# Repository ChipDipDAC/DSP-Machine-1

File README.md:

# DSP-Machine-1
Hi-Res Streamer - Power Amplifier for Raspberry Pi<br>
<a class="link" href="https://www.chipdip.ru/catalog-show/for-you-projects?p.0=ChipDipDac"><strong>DSP Machine 1</strong></a> - cтример, цифроаналоговый преобразователь ЦАП, аудиопроцессор, усилитель для микрокомпьютеров Raspberry Pi.<br />
Для построения стримера-усилителя вы можете использовать любой микрокомпьютер Raspberry Pi 2 или 3. Микрокомпьютер устанавливается на 40-пиновый разъем аудио карты. В качестве ПО используйте любой плеер или ОС образ, которых записан на микроSD карточку для Raspberry Pi. Операционные системы автоматически определяют аудиокарту ChipDip DAC и настраивают вывод звука именно на неё. В некоторых плеерах может понадобится выбрать в качестве устройства вывода звука - ChipDip DAC.<br />
<br />
- Plug and Play не требует пайки<br />
- Совместим с Raspberry Pi<br />
- Официальная поддержка RaspberryPi OS / Volumio3 / rAudio1 / Album Player / OpenELEC / Manjaro OS / MoOde и другими<br />
- DSP ADAU1701, чип усилителя TPA3255 для наилучшего качества звука.<br />
- Мощность 2х60 Вт<br />
- Разъемы аудиовыхода: две пары винтовых клемм (левый и правый)<br />
- Встроенная EEPROM для автоматической настройки ОС (с защитой от записи).<br />
- Автоматическое переключение частот в соответствии с входными сигналами I2S.<br />
- Диапазон частот дискретизации и разрядности от 44,1кГц/16 бит до 192кГц/32 бит<br />
- Совместим с ПО SigmaStudio и ChipStudio для перестройки аудиопроцессора<br />
<br />
Задать вопросы можно на форуме в разделе <a class="link" href="https://forum.chipdip.ru/index.php#chipdip-dac.39">ChipDip DAC</a>
<p></p>

<p></p>

<h2>Что под крышкой *</h2>

<p></p>

<p></p>
* Микрокомпьютер Raspberry Pi в комплект не входит.

<h2>Сравнительная таблица</h2>

<table class="user_t">
	<tbody>
		<tr>
			<td class="tcenter">&nbsp;</td>
			<td class="tcenter">DSP Machine 1</td>
			<td class="tcenter">DSP Machine 2</td>
			<td class="tcenter">DSP Machine 3</td>
		</tr>
		<tr>
			<td class="tcenter">Темброблок</td>
			<td class="tcenter">+</td>
			<td class="tcenter">+</td>
			<td class="tcenter">+</td>
		</tr>
		<tr>
			<td class="tcenter">SuperBass</td>
			<td class="tcenter">+</td>
			<td class="tcenter">+</td>
			<td class="tcenter">+</td>
		</tr>
		<tr>
			<td class="tcenter">Mute</td>
			<td class="tcenter">+</td>
			<td class="tcenter">+</td>
			<td class="tcenter">+</td>
		</tr>
		<tr>
			<td class="tcenter">Блок питания</td>
			<td class="tcenter">+</td>
			<td class="tcenter">+</td>
			<td class="tcenter">+</td>
		</tr>
		<tr>
			<td class="tcenter">Корректное выключение</td>
			<td class="tcenter">+</td>
			<td class="tcenter">+</td>
			<td class="tcenter">+</td>
		</tr>
		<tr>
			<td class="tcenter">Линейный выход</td>
			<td class="tcenter">-</td>
			<td class="tcenter">+</td>
			<td class="tcenter">+</td>
		</tr>
		<tr>
			<td class="tcenter">Усилитель мощности</td>
			<td class="tcenter">+</td>
			<td class="tcenter">-</td>
			<td class="tcenter">-</td>
		</tr>
		<tr>
			<td class="tcenter">Выход SPDIF</td>
			<td class="tcenter">-</td>
			<td class="tcenter">-</td>
			<td class="tcenter">+</td>
		</tr>
		<tr>
			<td class="tcenter">Выход Toslink</td>
			<td class="tcenter">-</td>
			<td class="tcenter">-</td>
			<td class="tcenter">+</td>
		</tr>
		<tr>
			<td class="tcenter">SigmaStudio</td>
			<td class="tcenter">+</td>
			<td class="tcenter">-</td>
			<td class="tcenter">+</td>
		</tr>
		<tr>
			<td class="tcenter">PurePathStudio</td>
			<td class="tcenter">-</td>
			<td class="tcenter">+</td>
			<td class="tcenter">-</td>
		</tr>
		<tr>
			<td class="tcenter">ChipStudio</td>
			<td class="tcenter">+</td>
			<td class="tcenter">+</td>
			<td class="tcenter">+</td>
		</tr>
	</tbody>
</table>
<br />

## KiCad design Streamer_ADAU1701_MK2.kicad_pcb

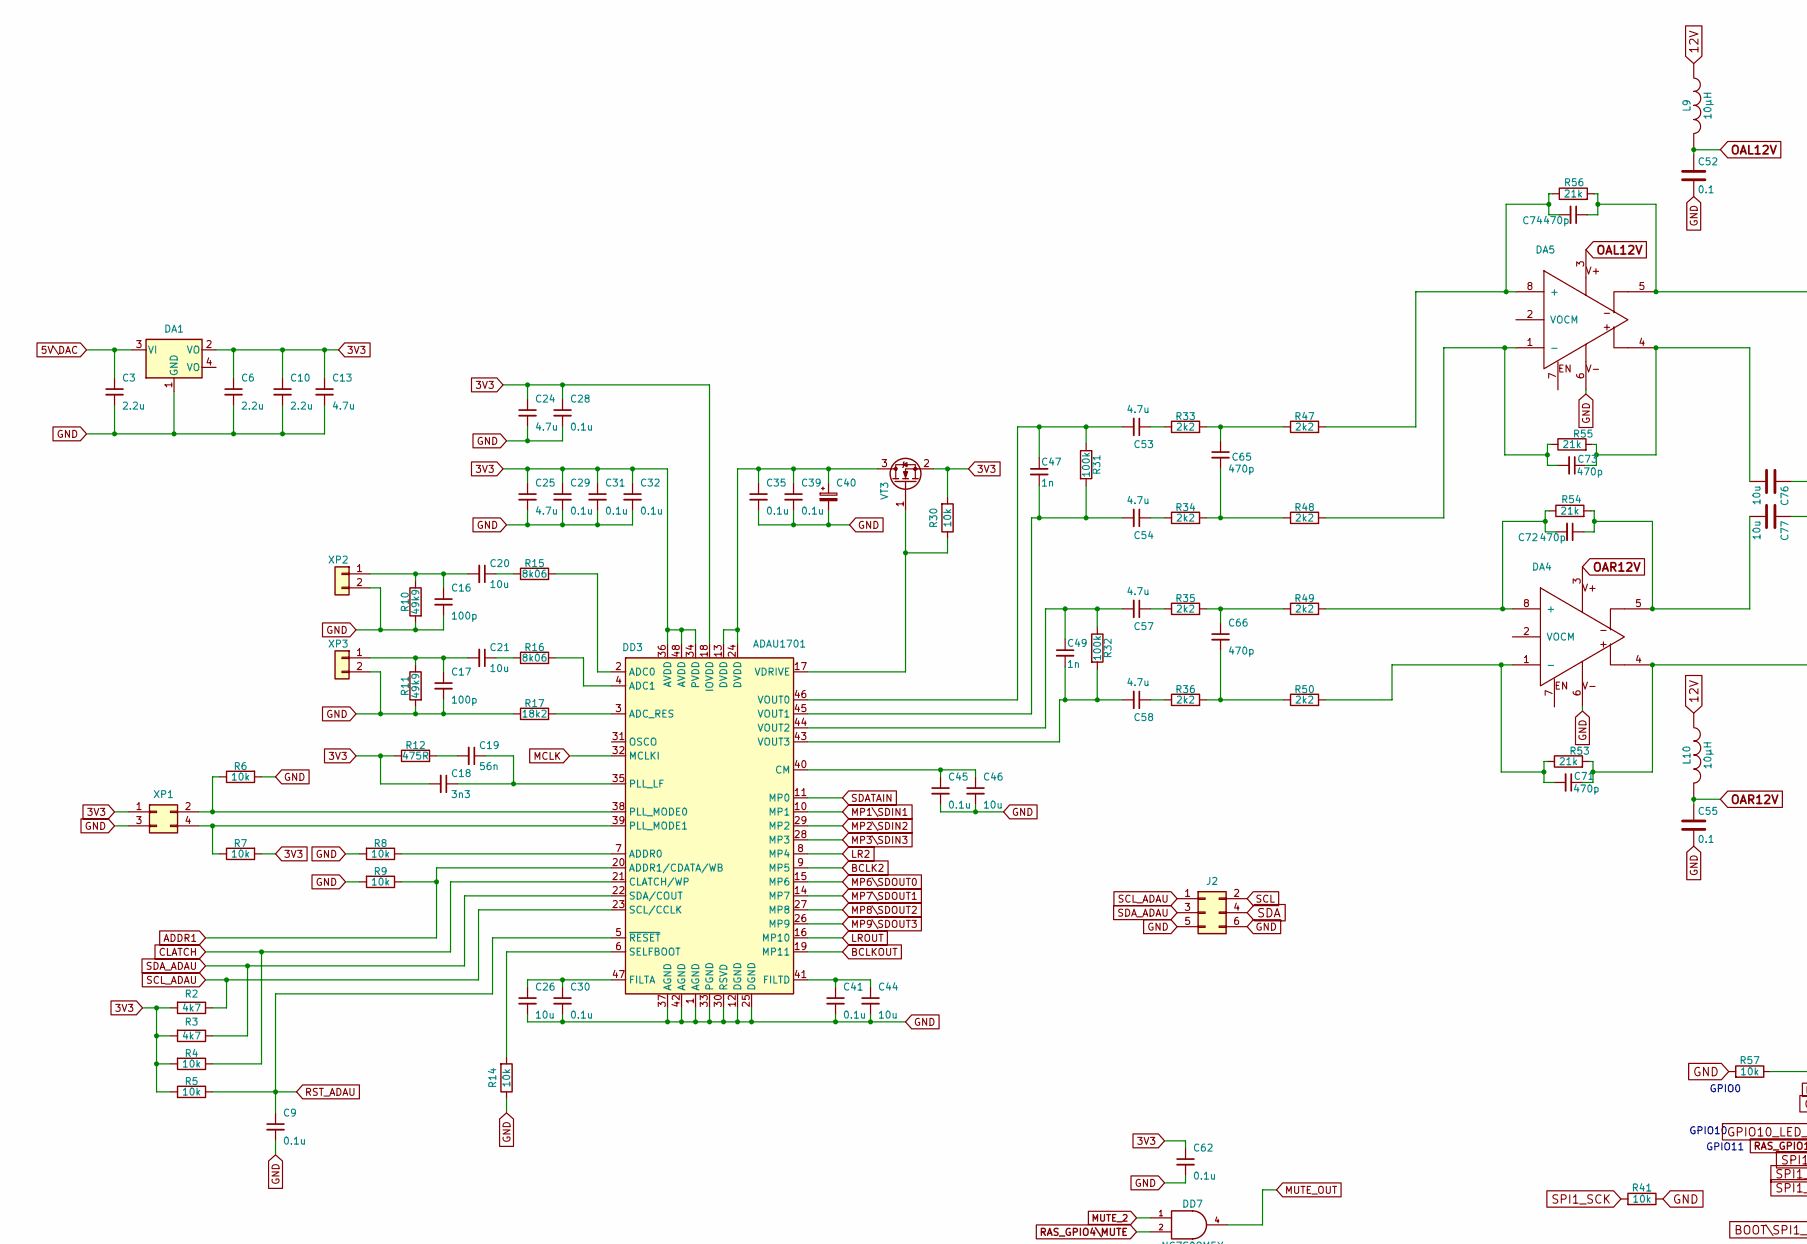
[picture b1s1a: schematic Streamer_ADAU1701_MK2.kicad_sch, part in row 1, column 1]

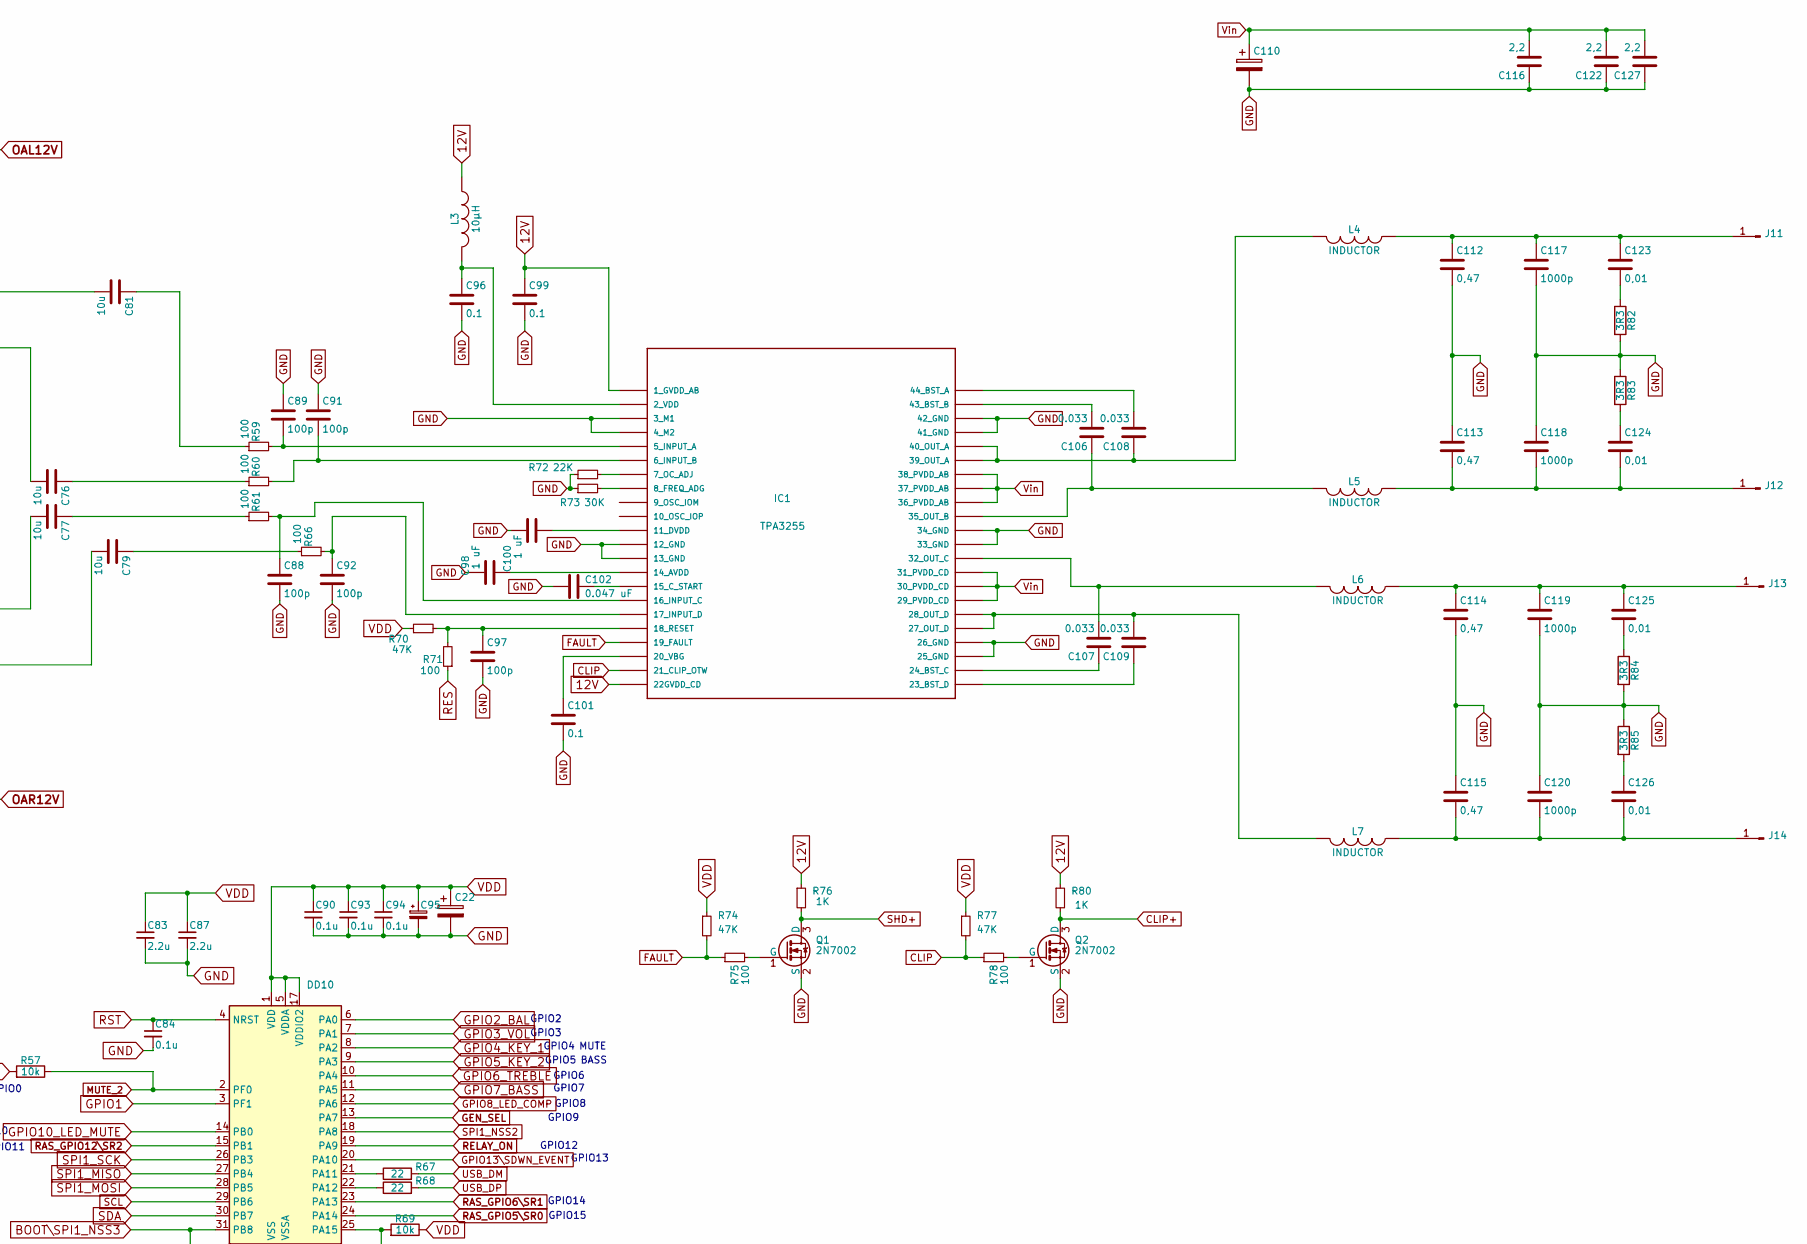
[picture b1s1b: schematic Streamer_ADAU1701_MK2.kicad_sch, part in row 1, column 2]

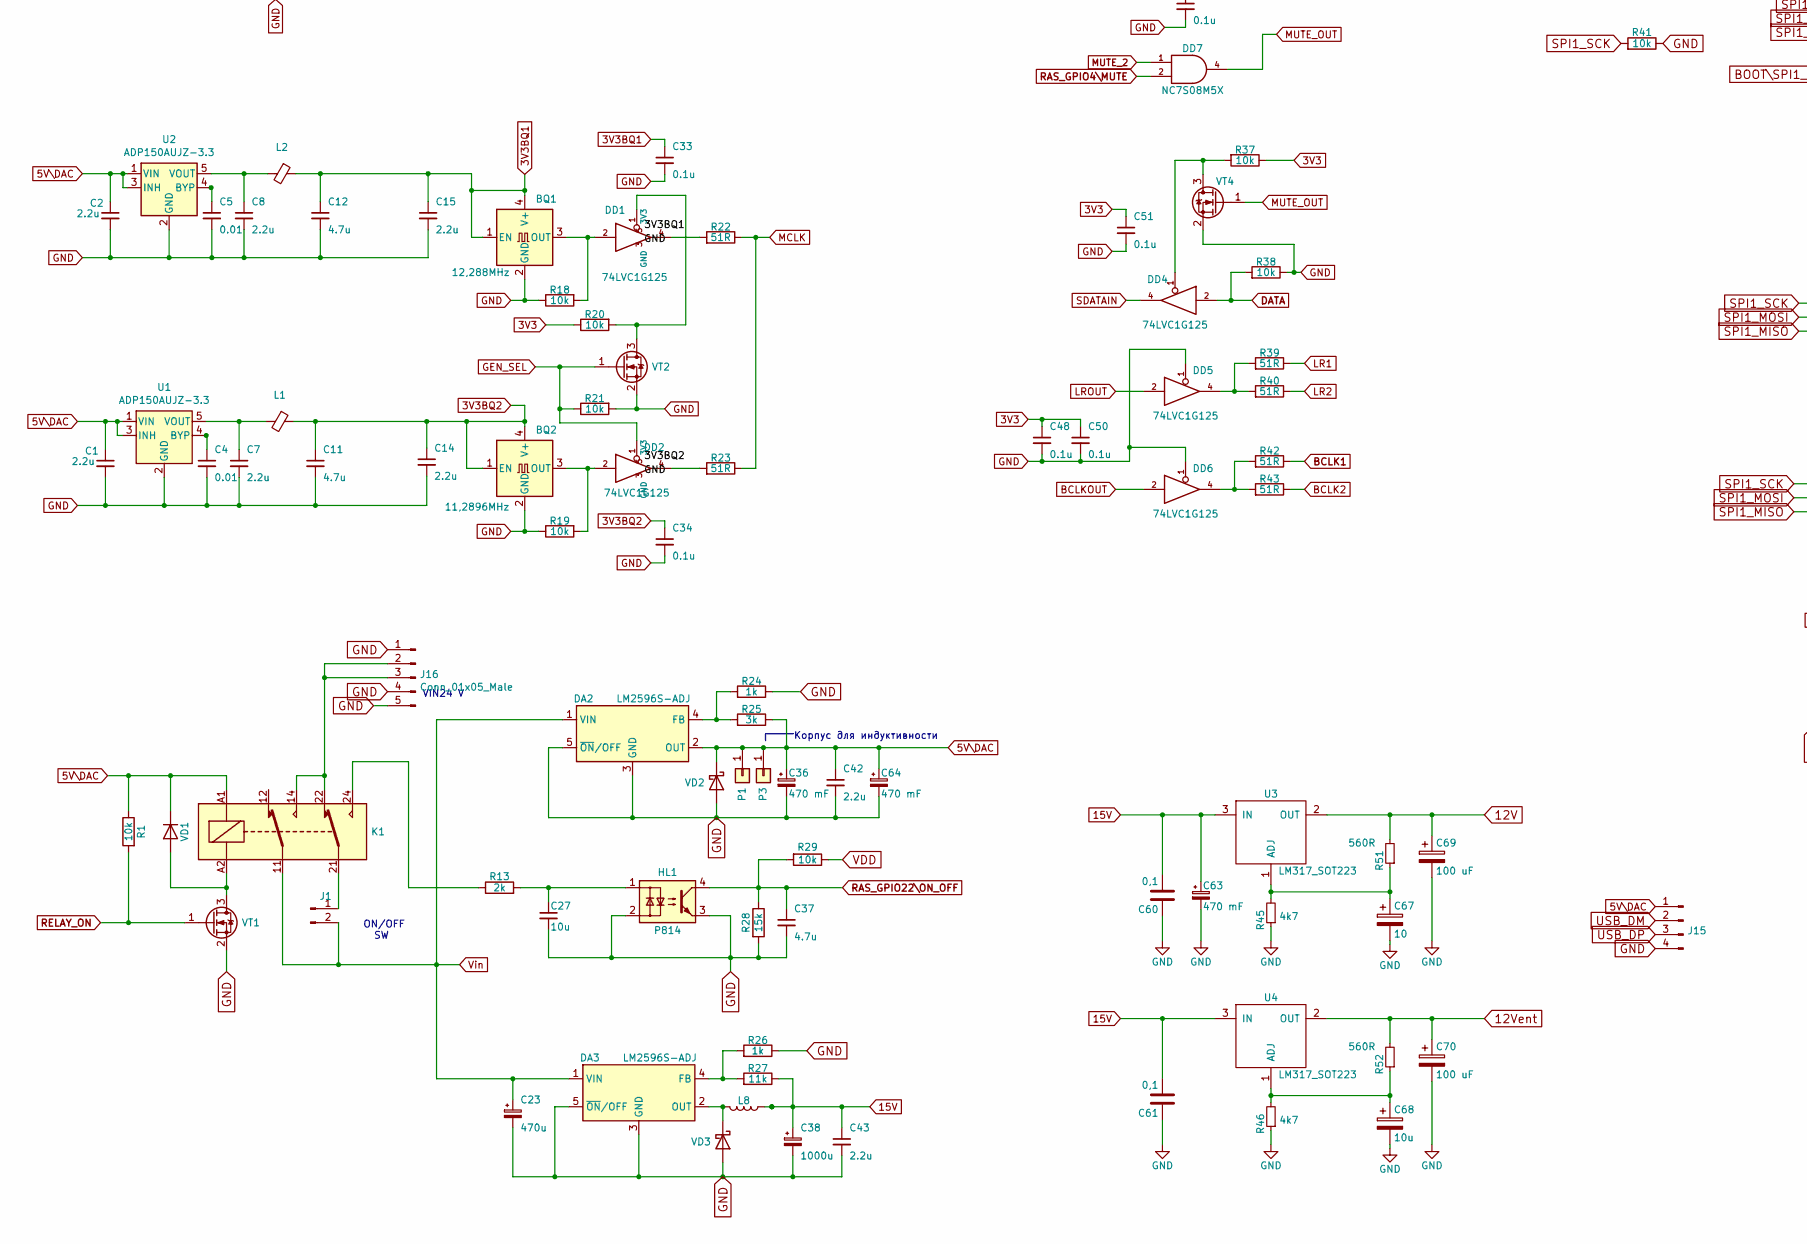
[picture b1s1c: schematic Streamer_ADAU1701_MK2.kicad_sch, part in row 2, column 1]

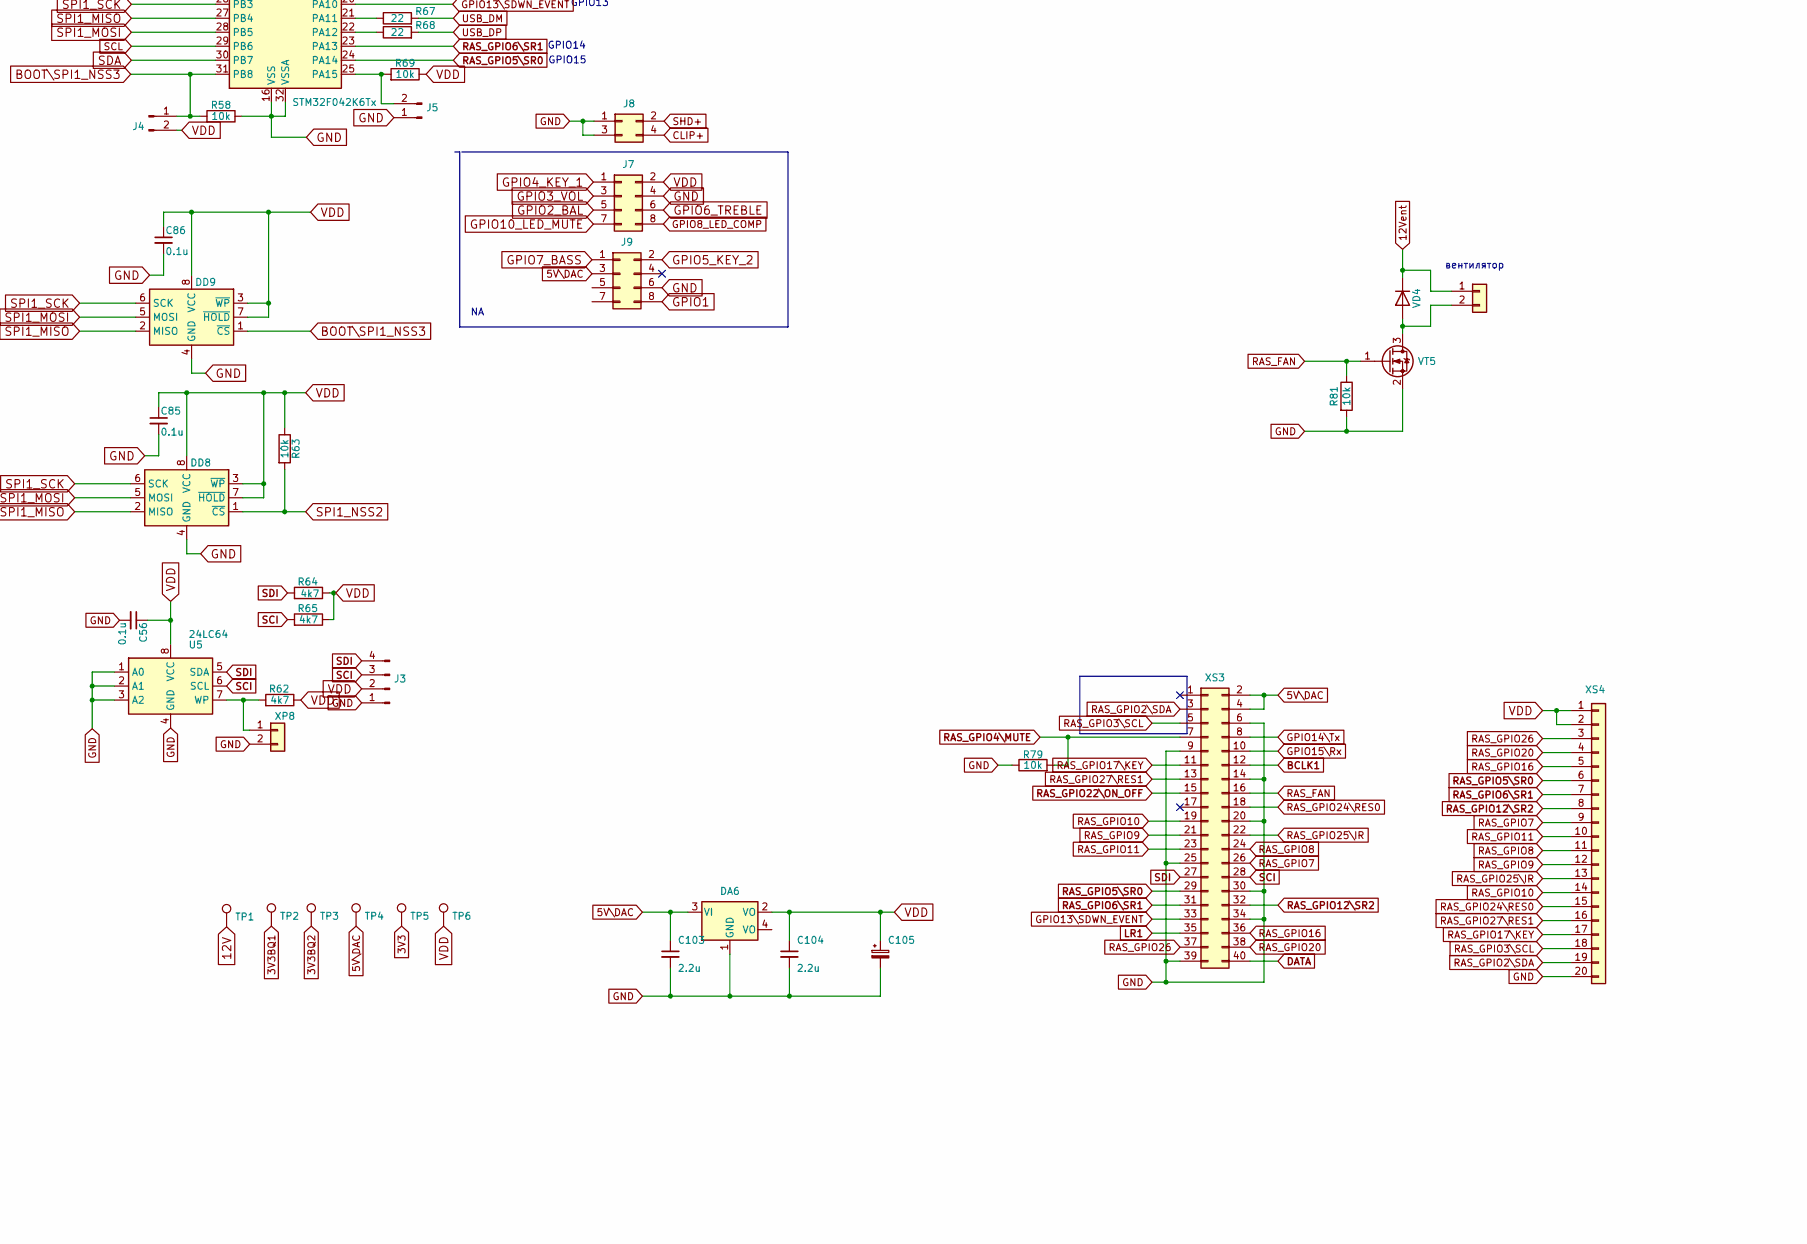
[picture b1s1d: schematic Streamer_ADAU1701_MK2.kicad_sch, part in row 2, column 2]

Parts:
BQ1: 12,288MHz; Oscillator_SMD_Fordahl_DFAS2-4Pin_7.3x5.1mm_HandSoldering
BQ2: 11,2896MHz; Oscillator_SMD_Fordahl_DFAS2-4Pin_7.3x5.1mm_HandSoldering
C1, C2, C3, C6, C7, C8, C10, C14, C15, C42, C43, C83, C87, C103, C104: 2.2u; C_0603_1608Metric_Pad1.05x0.95mm_HandSolder
C4, C5: 0.01; C_0603_1608Metric_Pad1.05x0.95mm_HandSolder
C9, C29, C30, C31, C32, C33, C34, C35, C39, C41, C45, C48, C50, C51, C56, C62, C84, C85, C86, C90, C93, C94: 0.1u; C_0603_1608Metric_Pad1.05x0.95mm_HandSolder
C11, C12, C13, C24, C25, C37: 4.7u; CP_EIA-3216-18_Kemet-A_Pad1.58x1.35mm_HandSolder
C16, C17, C88, C89, C91, C92, C97: 100p; C_0603_1608Metric_Pad1.05x0.95mm_HandSolder
C18: 3n3; C_0603_1608Metric_Pad1.05x0.95mm_HandSolder
C19: 56n; C_0603_1608Metric_Pad1.05x0.95mm_HandSolder
C20, C21, C26, C27, C44, C46: 10u; C_0603_1608Metric_Pad1.05x0.95mm_HandSolder
C22, C40, C95, C105, C110: (no value)
C23: 470u; CP_Radial_D10.0mm_P5.00mm
C28: 0.1u; C_0805_2012Metric
C36, C63, C64: 470 mF; CP_Radial_D10.0mm_P5.00mm
C38: 1000u; CP_Radial_D10.0mm_P5.00mm
C47, C49: 1n; C_Disc_D4.7mm_W2.5mm_P5.00mm
C52, C55, C96, C99, C101: 0.1; C_0603_1608Metric_Pad1.05x0.95mm_HandSolder
C53, C54, C57, C58: 4.7u; CP_Radial_D5.0mm_P2.50mm
C60, C61: 0,1; C_0603_1608Metric_Pad1.05x0.95mm_HandSolder
C65, C66: 470p; C_Disc_D4.7mm_W2.5mm_P5.00mm
C67: 10; C_Radial_D5.0mm_H11.0mm_P2.00mm
C68, C76, C77, C79, C81: 10u; C_Radial_D5.0mm_H11.0mm_P2.00mm
C69: 100 uF; CP_Radial_D10.0mm_P5.00mm
C70: 100 uF; CP_Radial_D6.3mm_P2.50mm
C71, C72, C73, C74: 470p; C_0603_1608Metric_Pad1.05x0.95mm_HandSolder
C98, C100: 1 uF; C_0603_1608Metric_Pad1.05x0.95mm_HandSolder
C102: 0.047 uF; C_0603_1608Metric_Pad1.05x0.95mm_HandSolder
C106, C107, C108, C109: 0.033; C_0603_1608Metric_Pad1.05x0.95mm_HandSolder
C112, C113, C114, C115: 0,47; C_Rect_L7.2mm_W3.5mm_P5.00mm_FKS2_FKP2_MKS2_MKP2
C116, C122, C127: 2,2; C_1210_3225Metric_Pad1.42x2.65mm_HandSolder
C117, C118, C119, C120: 1000p; C_1206_3216Metric_Pad1.42x1.75mm_HandSolder
C123, C124, C125, C126: 0,01; C_0805_2012Metric_Pad1.15x1.40mm_HandSolder
DA1, DA6: LM1117-3.3; SOT-223
DA2, DA3: LM2596S-ADJ; TO-263-5_TabPin3
DA4, DA5: OPA1632-NewComponents_KiCad; MSOP-8-1EP_3x3mm_P0.65mm_EP1.95x2.15mm_ThermalVias
DD1, DD2, DD4, DD5, DD6: 74LVC1G125; SOT-23-5
DD3: ADAU1701; LQFP-48_7x7mm_P0.5mm
DD7: NC7S08M5X; SOT-23-5
DD8, DD9: 25LCxxx; SOIC-8_5.23x5.23mm_P1.27mm
DD10: STM32F042K6Tx; LQFP-32_7x7mm_P0.8mm
HL1: P814; DIP-4_W7.62mm
IC1: TPA3255; TSSOP-44_TPA255
J1, J4, J5: Conn_01x02_Male; PinHeader_1x02_P2.54mm_Vertical
J2: Conn_02x03_Odd_Even; PinHeader_2x03_P2.54mm_Vertical
J3, J15: Conn_01x04_Male; PinHeader_1x04_P2.54mm_Vertical
J7, J9: Conn_02x04_Odd_Even; PinHeader_2x04_P2.54mm_Vertical
J8: Conn_02x02_Odd_Even; PinHeader_2x02_P2.54mm_Vertical
J11, J12, J13, J14: Conn_01x01_Male; MountingHole_2.2mm_M2
J16: Conn_01x05_Male; BarrelJack_PD-40
K1: RTE2xxxx; Relay_DPDT_Schrack-RT2-FormC_RM5mm
L1, L2: (no value)
L3, L9, L10: 10μH; L_0603_1608Metric_Pad1.05x0.95mm_HandSolder
L4, L5, L6, L7: INDUCTOR; L_Toroid_Vertical_L21.6mm_W11.4mm_P7.62mm_Pulse_KM-3
L8: MMZ2012S601AT000; L_Radial_D7.8mm_P5.00mm_Fastron_07HCP
P1, P3: Conn_01x01; TestPoint_Keystone_5005-5009_Compact
Q1, Q2: 2N7002; TSOT-23
R1, R4, R5, R6, R7, R8, R9, R14, R18, R19, R20, R21, R29, R30, R37, R38, R57, R58, R63, R69, R79, R81: 10k; R_0603_1608Metric_Pad1.05x0.95mm_HandSolder
R2, R3, R45, R46, R62, R64, R65: 4k7; R_0603_1608Metric_Pad1.05x0.95mm_HandSolder
R10, R11: 49k9; R_0603_1608Metric_Pad1.05x0.95mm_HandSolder
R12: 475R; R_0603_1608Metric_Pad1.05x0.95mm_HandSolder
R13: 2k; R_0603_1608Metric_Pad1.05x0.95mm_HandSolder
R15, R16: 8k06; R_0603_1608Metric_Pad1.05x0.95mm_HandSolder
R17: 18k2; R_0603_1608Metric_Pad1.05x0.95mm_HandSolder
R22, R23, R39, R40, R42, R43: 51R; R_0603_1608Metric_Pad1.05x0.95mm_HandSolder
R24, R26: 1k; R_0603_1608Metric_Pad1.05x0.95mm_HandSolder
R25: 3k; R_0603_1608Metric_Pad1.05x0.95mm_HandSolder
R27: 11k; R_0603_1608Metric_Pad1.05x0.95mm_HandSolder
R28: 15k; R_0603_1608Metric_Pad1.05x0.95mm_HandSolder
R31, R32: 100k; R_0603_1608Metric_Pad1.05x0.95mm_HandSolder
R33, R34, R35, R36, R47, R48, R49, R50: 2k2; R_0603_1608Metric_Pad1.05x0.95mm_HandSolder
R41: 10k; R_0603_1608Metric_Pad0.98x0.95mm_HandSolder
R51, R52: 560R; R_0603_1608Metric_Pad1.05x0.95mm_HandSolder
R53, R54, R55, R56: 21k; R_Axial_DIN0204_L3.6mm_D1.6mm_P5.08mm_Horizontal
R59, R60, R61, R66, R71, R75, R78: 100; R_0603_1608Metric_Pad1.05x0.95mm_HandSolder
R67, R68: 22; R_0603_1608Metric_Pad1.05x0.95mm_HandSolder
R70, R74, R77: 47K; R_0603_1608Metric_Pad1.05x0.95mm_HandSolder
R72: 22K; R_0603_1608Metric_Pad1.05x0.95mm_HandSolder
R73: 30K; R_0603_1608Metric_Pad1.05x0.95mm_HandSolder
R76, R80: 1K; R_0603_1608Metric_Pad1.05x0.95mm_HandSolder
R82, R83, R84, R85: 3R3; R_0805_2012Metric_Pad1.15x1.40mm_HandSolder
TP1, TP2, TP3, TP4, TP5, TP6: TestPoint; TestPoint_Pad_D1.5mm
U1, U2: ADP150AUJZ-3.3; SOT-23-5
U3, U4: LM317_SOT223; SOT-223
U5: 24LC64; SOIC-8_3.9x4.9mm_P1.27mm
VD1, VD4: D; D_SOD-123
VD2, VD3: D_Schottky; D_SMC_Handsoldering
VT1, VT2, VT3, VT4, VT5: BSS138; SOT-23
XP1: Conn_02x02_Odd_Even; PinHeader_2x02_P2.54mm_Vertical
XP2, XP3, XP8, XP9: Conn_01x02; PinHeader_1x02_P2.54mm_Vertical
XS3: Conn_02x20_Odd_Even; PinSocket_2x20_P2.54mm_Vertical
XS4: Conn_01x20; Hirose_FH12-20S-0.5SH_1x20-1MP_P0.50mm_Horizontal

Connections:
3V3: C6.1, C10.1, C13.1, C18.2, C24.1, C25.1, C28.1, C29.1, C31.1, C32.1, C48.1, C50.1, C51.1, C62.1, DA1.2 (VO), DD3.18 (IOVDD), DD3.34 (PVDD), DD3.36 (AVDD), DD3.48 (AVDD), DD4.5 (3V3), DD5.5 (3V3), DD6.5 (3V3), DD7.5 (3V3), R2.2, R3.2, R4.2, R5.2, R7.2, R12.1, R20.1, R30.2, R37.1, TP5.1, VT3.2 (S), XP1.1
3V3BQ1: BQ1.1 (EN), BQ1.4 (V+), C12.1, C15.1, C33.1, DD1.5 (3V3), L2.1, TP2.1
3V3BQ2: BQ2.1 (EN), BQ2.4 (V+), C11.1, C14.1, C34.1, DD2.5 (3V3), L1.1, TP3.1
5V\DAC: C1.1, C2.1, C3.1, C36.1, C42.1, C64.1, C103.1, DA1.3 (VI), DA2.2 (OUT), DA6.3 (VI), J9.3, J15.1, K1.A1, P1.1, P3.1, R1.1, R25.1, TP4.1, U1.1 (VIN), U1.3 (INH), U2.1 (VIN), U2.3 (INH), VD1.1 (K), VD2.1 (K), XS3.2, XS3.4
12V: C69.1, C99.1, IC1.1 (1_GVDD_AB), IC1.22 (22GVDD_CD), L3.1, L9.1, L10.1, R51.2, R76.1, R80.1, TP1.1, U3.2 (OUT)
12Vent: C70.1, R52.2, U4.2 (OUT), VD4.1 (K), XP9.1
15V: C38.1, C43.1, C60.2, C61.2, C63.1, L8.1, R27.1, U3.3 (IN), U4.3 (IN); also elsewhere on the board
ADDR1: DD3.20 (ADDR1/CDATA/WB), R9.1
BCLK1: R42.1, XS3.12
BCLK2: DD3.9 (MP5), R43.1
BCLKOUT: DD3.19 (MP11), DD6.2
BOOT\SPI1_NSS3: DD9.1 (~CS), DD10.31 (PB8), J4.1, R58.2
CLATCH: DD3.21 (CLATCH/WP), R4.1
CLIP: IC1.21 (21_CLIP_OTW), R77.2, R78.1
CLIP+: J8.4, Q2.3 (D), R80.2
DATA: DD4.2, R38.2, XS3.40
FAULT: IC1.19 (19_FAULT), R74.2, R75.1
GEN_SEL: DD2.1, DD10.13 (PA7), R21.1, VT2.1 (G)
GND: BQ1.2 (GND), BQ2.2 (GND), C1.2, C2.2, C3.2, C4.2, C5.2, C6.2, C7.2, C8.2, C9.2, C10.2, C11.2, C12.2, C13.2, C14.2, C15.2, C16.2, C17.2, C22.2, C23.2, C24.2, C25.2, C26.2, C27.2, C28.2, C29.2, C30.2, C31.2, C32.2, C33.2, C34.2, C35.2, C36.2, C37.2, C38.2, C39.2, C40.2, C41.2, C42.2, C43.2, C44.2, C45.2, C46.2, C48.2, C50.2, C51.2, C52.2, C55.2, C56.2, C60.1, C61.1, C62.2, C63.2, C64.2, C67.2, C68.2, C69.2, C70.2, C83.2, C84.2, C85.2, C86.2, C87.2, C88.2, C89.1, C90.2, C91.1, C92.2, C93.2, C94.2, C95.2, C96.2, C97.2, C98.2, C99.2, C100.2, C101.2, C102.2, C103.2, C104.2, C105.2, C110.2, C112.2, C113.1, C114.2, C115.1, C116.1, C117.2, C118.1, C119.2, C120.1, C122.1, C127.1, DA1.1 (GND), DA2.3 (GND), DA2.5 (~ON/OFF), DA3.3 (GND), DA3.5 (~ON/OFF), DA4.6, DA5.6, DA6.1 (GND), DD1.3 (GND), DD2.3 (GND), DD3.1 (AGND), DD3.12 (DGND), DD3.25 (DGND), DD3.30 (RSVD), DD3.33 (PGND), DD3.37 (AGND), DD3.42 (AGND), DD4.3 (GND), DD5.1, DD5.3 (GND), DD6.1, DD6.3 (GND), DD7.3 (GND), DD8.4 (GND), DD9.4 (GND), DD10.16 (VSS), DD10.32 (VSSA), HL1.2, HL1.3, IC1.3 (3_M1), IC1.4 (4_M2), IC1.12 (12_GND), IC1.13 (13_GND), IC1.25 (25_GND), IC1.26 (26_GND), IC1.33 (33_GND), IC1.34 (34_GND), IC1.41 (41_GND), IC1.42 (42_GND), J2.5, J2.6, J3.1, J5.1, J7.4, J8.1, J8.3, J9.6, J15.4, J16.1, J16.4, J16.5, Q1.2 (S), Q2.2 (S), R6.2, R8.2, R9.2, R10.2, R11.2, R14.1, R17.1, R18.1, R19.1, R21.2, R24.1, R26.1, R28.2, R38.1, R41.1, R45.1, R46.1, R57.2, R58.1, R72.1, R73.1, R79.1, R81.2, R82.2, R83.1, R84.2, R85.1, U1.2 (GND), U2.2 (GND), U5.1 (A0), U5.2 (A1), U5.3 (A2), U5.4 (GND), VD2.2 (A), VD3.2 (A), VT1.2 (S), VT2.2 (S), VT4.2 (S), VT5.2 (S), XP1.3, XP2.2, XP3.2, XP8.2, XS3.6, XS3.9, XS3.14, XS3.20, XS3.25, XS3.30, XS3.34, XS3.39, XS4.20
GPIO1: DD10.3 (PF1), J9.8
GPIO2_BAL: DD10.6 (PA0), J7.5
GPIO3_VOL: DD10.7 (PA1), J7.3
GPIO4_KEY_1: DD10.8 (PA2), J7.1
GPIO5_KEY_2: DD10.9 (PA3), J9.2
GPIO6_TREBLE: DD10.10 (PA4), J7.6
GPIO7_BASS: DD10.11 (PA5), J9.1
GPIO8_LED_COMP: DD10.12 (PA6), J7.8
GPIO10_LED_MUTE: DD10.14 (PB0), J7.7
GPIO13\SDWN_EVENT: DD10.20 (PA10), XS3.33
GPIO14\Tx: XS3.8
GPIO15\Rx: XS3.10
LR1: R39.1, XS3.35
LR2: DD3.8 (MP4), R40.1
LROUT: DD3.16 (MP10), DD5.2
MCLK: DD3.32 (MCLKI), R22.1, R23.1
MP1\SDIN1: DD3.10 (MP1)
MP2\SDIN2: DD3.29 (MP2)
MP3\SDIN3: DD3.28 (MP3)
MP6\SDOUT0: DD3.15 (MP6)
MP7\SDOUT1: DD3.14 (MP7)
MP8\SDOUT2: DD3.27 (MP8)
MP9\SDOUT3: DD3.26 (MP9)
MUTE_2: DD7.1, DD10.2 (PF0), R57.1
MUTE_OUT: DD7.4, VT4.1 (G)
unnamed: BQ1.3 (OUT), DD1.2, R18.2
unnamed: BQ2.3 (OUT), DD2.2, R19.2
unnamed: C4.1, U1.4 (BYP)
unnamed: C5.1, U2.4 (BYP)
unnamed: C7.1, L1.2, U1.5 (VOUT)
unnamed: C8.1, L2.2, U2.5 (VOUT)
unnamed: C16.1, C20.2, R10.1, XP2.1
unnamed: C17.1, C21.2, R11.1, XP3.1
unnamed: C18.1, C19.1, DD3.35 (PLL_LF)
unnamed: C19.2, R12.2
unnamed: C20.1, R15.1
unnamed: C21.1, R16.1
unnamed: C26.1, C30.1, DD3.47 (FILTA)
unnamed: C27.1, HL1.1, R13.2
unnamed: C35.1, C39.1, C40.1, DD3.13 (DVDD), DD3.24 (DVDD), VT3.3 (D)
unnamed: C41.1, C44.1, DD3.41 (FILTD)
unnamed: C45.1, C46.1, DD3.40 (CM)
unnamed: C47.1, C53.2, DD3.46 (VOUT0), R31.1
unnamed: C47.2, C54.2, DD3.45 (VOUT1), R31.2
unnamed: C49.1, C57.2, DD3.44 (VOUT2), R32.1
unnamed: C49.2, C58.2, DD3.43 (VOUT3), R32.2
unnamed: C53.1, R33.1
unnamed: C54.1, R34.1
unnamed: C57.1, R35.1
unnamed: C58.1, R36.1
unnamed: C65.1, R33.2, R47.1
unnamed: C65.2, R34.2, R48.1
unnamed: C66.1, R35.2, R49.1
unnamed: C66.2, R36.2, R50.1
unnamed: C67.1, R45.2, R51.1, U3.1 (ADJ)
unnamed: C68.1, R46.2, R52.1, U4.1 (ADJ)
unnamed: C71.1, C79.2, DA4.4, R53.2
unnamed: C71.2, DA4.1 (-), R50.2, R53.1
unnamed: C72.1, C77.2, DA4.5, R54.2
unnamed: C72.2, DA4.8 (+), R49.2, R54.1
unnamed: C73.1, C76.2, DA5.4, R55.2
unnamed: C73.2, DA5.1 (-), R48.2, R55.1
unnamed: C74.1, C81.2, DA5.5, R56.2
unnamed: C74.2, DA5.8 (+), R47.2, R56.1
unnamed: C76.1, R60.1
unnamed: C77.1, R61.1
unnamed: C79.1, R66.1
unnamed: C81.1, R59.1
unnamed: C88.1, IC1.16 (16_INPUT_C), R61.2
unnamed: C89.2, IC1.5 (5_INPUT_A), R59.2
unnamed: C91.2, IC1.6 (6_INPUT_B), R60.2
unnamed: C92.1, IC1.17 (17_INPUT_D), R66.2
unnamed: C96.1, IC1.2 (2_VDD), L3.2
unnamed: C97.1, IC1.18 (18_RESET), R70.2, R71.2
unnamed: C98.1, IC1.14 (14_AVDD)
unnamed: C100.1, IC1.11 (11_DVDD)
unnamed: C101.1, IC1.20 (20_VBG)
unnamed: C102.1, IC1.15 (15_C_START)
unnamed 97: C106.1, IC1.35 (35_OUT_B), L5.2; also elsewhere on the board
unnamed: C106.2, IC1.43 (43_BST_B)
unnamed: C107.1, IC1.24 (24_BST_C)
unnamed 100: C107.2, IC1.32 (32_OUT_C), L6.2; also elsewhere on the board
unnamed 101: C108.1, IC1.39 (39_OUT_A), IC1.40 (40_OUT_A), L4.2; also elsewhere on the board
unnamed: C108.2, IC1.44 (44_BST_A)
unnamed: C109.1, IC1.23 (23_BST_D)
unnamed 104: C109.2, IC1.27 (27_OUT_D), IC1.28 (28_OUT_D), L7.2; also elsewhere on the board
unnamed 105: C112.1, C117.1, C123.1, J11.1, J11.J11, L4.1; also elsewhere on the board
unnamed 106: C113.2, C118.2, C124.2, J12.1, L5.1; also elsewhere on the board
unnamed 107: C114.1, C119.1, C125.1, J13.1, L6.1; also elsewhere on the board
unnamed 108: C115.2, C120.2, C126.2, J14.1, L7.1; also elsewhere on the board
unnamed: C123.2, R82.1
unnamed: C124.1, R83.2
unnamed: C125.2, R84.1
unnamed: C126.1, R85.2
unnamed: DA2.4 (FB), R24.2, R25.2
unnamed: DA3.4 (FB), R26.2, R27.2
unnamed: DD1.1, R20.2, VT2.3 (D)
unnamed: DD1.4, R22.2
unnamed: DD2.4, R23.2
unnamed: DD3.2 (ADC0), R15.2
unnamed: DD3.3 (ADC_RES), R17.2
unnamed: DD3.4 (ADC1), R16.2
unnamed: DD3.6 (SELFBOOT), R14.2
unnamed: DD3.7 (ADDR0), R8.1
unnamed: DD3.17 (VDRIVE), R30.1, VT3.1 (G)
unnamed: DD3.38 (PLL_MODE0), R6.1, XP1.2
unnamed: DD3.39 (PLL_MODE1), R7.1, XP1.4
unnamed: DD4.1, R37.2, VT4.3 (D)
unnamed: DD5.4, R39.2, R40.2
unnamed: DD6.4, R42.2, R43.2
unnamed: DD10.21 (PA11), R67.1
unnamed: DD10.22 (PA12), R68.1
unnamed: DD10.25 (PA15), J5.2, R69.2
unnamed: IC1.7 (7_OC_ADJ), R72.2
unnamed: IC1.8 (8_FREQ_ADG), R73.2
unnamed: J1.1, K1.21
unnamed: J16.2, J16.3, K1.14, K1.22
unnamed: K1.24, R13.1
unnamed: K1.A2, VD1.2 (A), VT1.3 (D)
unnamed: Q1.1 (G), R75.2
unnamed: Q2.1 (G), R78.2
unnamed: R62.2, U5.7 (WP), XP8.1
unnamed: VD4.2 (A), VT5.3 (D), XP9.2
OAL12V: C52.1, DA5.3, L9.2
OAR12V: C55.1, DA4.3, L10.2
RAS_FAN: R81.1, VT5.1 (G), XS3.16
RAS_GPIO2\SDA: XS3.3, XS4.19
RAS_GPIO3\SCL: XS3.5, XS4.18
RAS_GPIO4\MUTE: DD7.2, R79.2, XS3.7
RAS_GPIO5\SR0: DD10.24 (PA14), XS3.29, XS4.6
RAS_GPIO6\SR1: DD10.23 (PA13), XS3.31, XS4.7
RAS_GPIO7: XS3.26, XS4.9
RAS_GPIO8: XS3.24, XS4.11
RAS_GPIO9: XS3.21, XS4.12
RAS_GPIO10: XS3.19, XS4.14
RAS_GPIO11: XS3.23, XS4.10
RAS_GPIO12\SR2: DD10.15 (PB1), XS3.32, XS4.8
RAS_GPIO16: XS3.36, XS4.5
RAS_GPIO17\KEY: XS3.11, XS4.17
RAS_GPIO20: XS3.38, XS4.4
RAS_GPIO22\ON_OFF: C37.1, HL1.4, R28.1, R29.2, XS3.15
RAS_GPIO24\RES0: XS3.18, XS4.15
RAS_GPIO25\IR: XS3.22, XS4.13
RAS_GPIO26: XS3.37, XS4.3
RAS_GPIO27\RES1: XS3.13, XS4.16
RELAY_ON: DD10.19 (PA9), R1.2, VT1.1 (G)
RES: R71.1
RST: C84.1, DD10.4 (NRST)
RST_ADAU: C9.1, DD3.5 (~RESET), R5.1
SCI: J3.3, R65.2, U5.6 (SCL), XS3.28
SCL: DD10.29 (PB6), J2.2
SCL_ADAU: DD3.23 (SCL/CCLK), J2.1, R2.1
SDA: DD10.30 (PB7), J2.4
SDATAIN: DD3.11 (MP0), DD4.4
SDA_ADAU: DD3.22 (SDA/COUT), J2.3, R3.1
SDI: J3.4, R64.2, U5.5 (SDA), XS3.27
SHD+: J8.2, Q1.3 (D), R76.2
SPI1_MISO: DD8.2 (MISO), DD9.2 (MISO), DD10.27 (PB4)
SPI1_MOSI: DD8.5 (MOSI), DD9.5 (MOSI), DD10.28 (PB5)
SPI1_NSS2: DD8.1 (~CS), DD10.18 (PA8), R63.2
SPI1_SCK: DD8.6 (SCK), DD9.6 (SCK), DD10.26 (PB3), R41.2
USB_DM: J15.2, R67.2
USB_DP: J15.3, R68.2
VDD: C22.1, C56.1, C83.1, C85.1, C86.1, C87.1, C90.1, C93.1, C94.1, C95.1, C104.1, C105.1, DA6.2 (VO), DD8.3 (~WP), DD8.7 (~HOLD), DD8.8 (VCC), DD9.3 (~WP), DD9.7 (~HOLD), DD9.8 (VCC), DD10.1 (VDD), DD10.5 (VDDA), DD10.17 (VDDIO2), J3.2, J4.2, J7.2, R29.1, R62.1, R63.1, R64.1, R65.1, R69.1, R70.1, R74.1, R77.1, TP6.1, U5.8 (VCC), XS4.1, XS4.2
Vin: C23.1, C110.1, C116.2, C122.2, C127.2, DA2.1 (VIN), DA3.1 (VIN), IC1.29 (29_PVDD_CD), IC1.30 (30_PVDD_CD), IC1.31 (31_PVDD_CD), IC1.36 (36_PVDD_AB), IC1.37 (37_PVDD_AB), IC1.38 (38_PVDD_AB), J1.2, K1.11

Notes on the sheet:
вентилятор
Корпус для индуктивности
GPIO9
GPIO0
GPIO12
BASS
GPIO2
GPIO15
GPIO14
MUTE
GPIO11
GPIO3
GPIO4
GPIO10
GPIO13
GPIO8
GPIO7
GPIO5
GPIO6
VIN24 V
ON/OFF SW

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
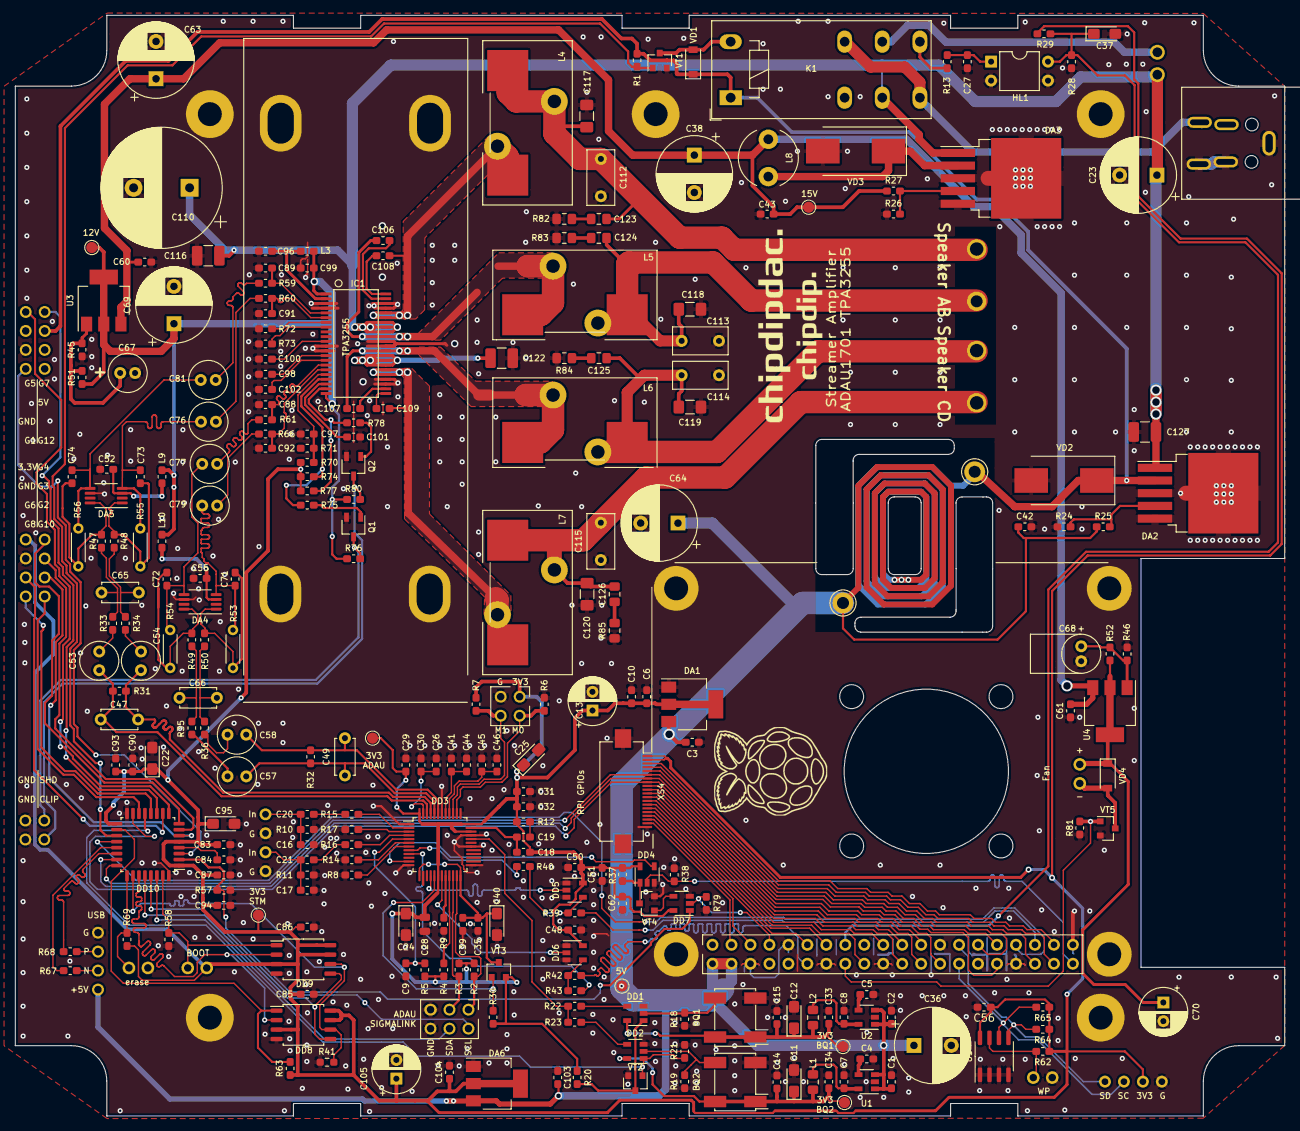
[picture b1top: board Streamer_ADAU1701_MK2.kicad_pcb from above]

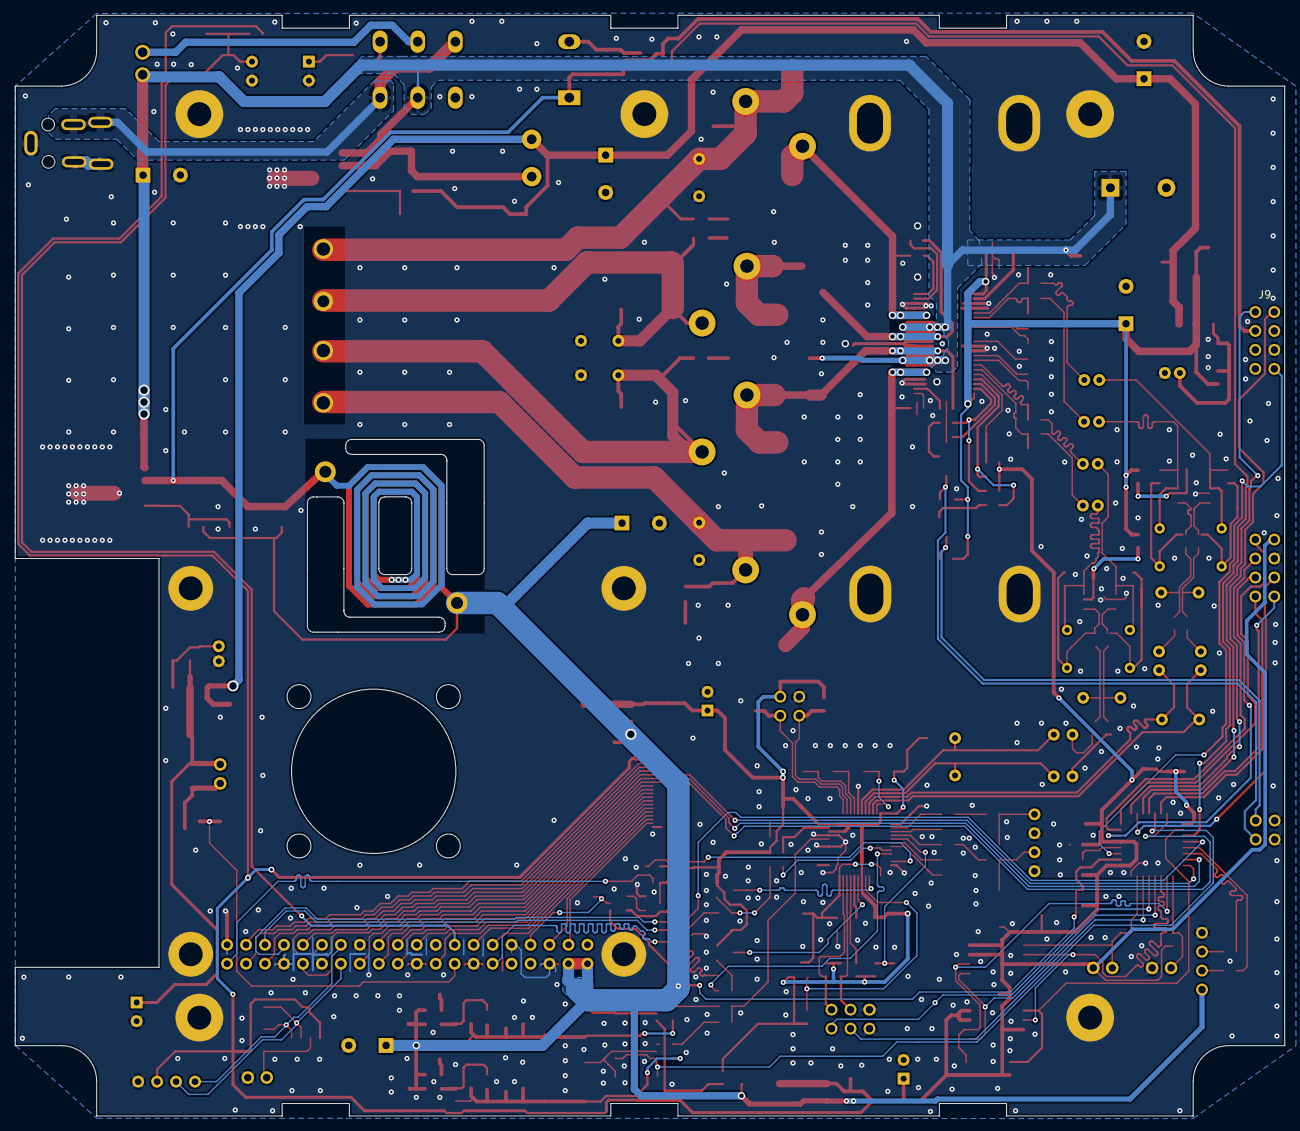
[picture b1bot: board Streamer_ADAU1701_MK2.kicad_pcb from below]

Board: 4 copper layers, 170.0 x 147.4 mm, 285 parts (2 on the bottom side), 175 nets.

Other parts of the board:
L3#2, L3#3, L3#4, L3#5: INDUCTOR; L_0029v2
TP4#2: TestPoint; TestPoint_Pad_D1.5mm

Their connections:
15V: TP4#2.1; also elsewhere on the board
unnamed 97: L3#4.1; also elsewhere on the board
unnamed 100: L3#5.1; also elsewhere on the board
unnamed 101: L3#2.2; also elsewhere on the board
unnamed 104: L3#3.2; also elsewhere on the board
unnamed 105: L3#2.1; also elsewhere on the board
unnamed 106: L3#4.2; also elsewhere on the board
unnamed 107: L3#5.2; also elsewhere on the board
unnamed 108: L3#3.1; also elsewhere on the board
